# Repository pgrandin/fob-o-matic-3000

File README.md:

# fob-o-matic-3000
The Fob-O-Matic 3000

At my favorite Hackerspace, Ace Monster Toys (https://www.acemonstertoys.org/), members get 24x7 access using their fob.

When a new member wants to join the community, we need an easy way to assign them a fob. Our fobs are pre-bundled in
individual enveloppes with the sign-in instructions. This tool is a simple project that allows us to quickly get the fob
number when we are preparing a batch of keys.

The box was 3D printed and designed for this project. 

Parts list :
 - 1 Arduino Uno R3 (https://www.amazon.com/Arduino-Uno-R3-Microcontroller-A000066/dp/B008GRTSV6) 
 - 1 cheap Oled display (https://www.amazon.com/gp/product/B00O2LLT30)
 - 1 Parallax RFID reader (https://www.amazon.com/gp/product/B00B88HFPG). 

The result:

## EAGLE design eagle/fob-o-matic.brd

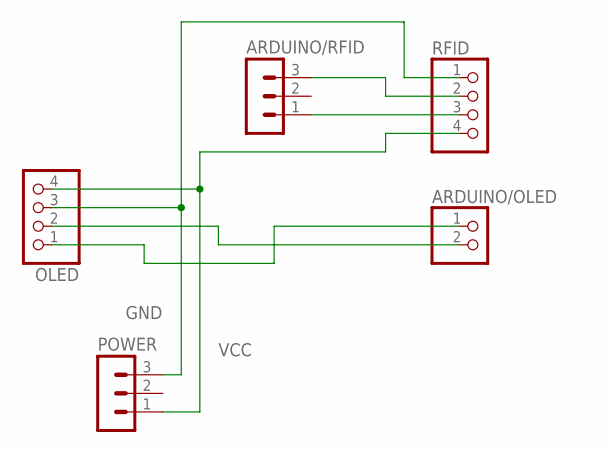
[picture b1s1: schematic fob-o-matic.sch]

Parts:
ARDUINO/OLED: PINHD-1X2; 1X02
ARDUINO/RFID: MA03-1
OLED: PINHD-1X4/90; 1X04/90
POWER: MA03-1
RFID: PINHD-1X4/90; 1X04/90

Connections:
/ENABLE: ARDUINO/RFID.1, RFID.3
GND: OLED.3, POWER.3, RFID.1
RX: ARDUINO/RFID.3, RFID.2
SCL: ARDUINO/OLED.2, OLED.2
SDA: ARDUINO/OLED.1, OLED.1
VCC: OLED.4, POWER.1, RFID.4

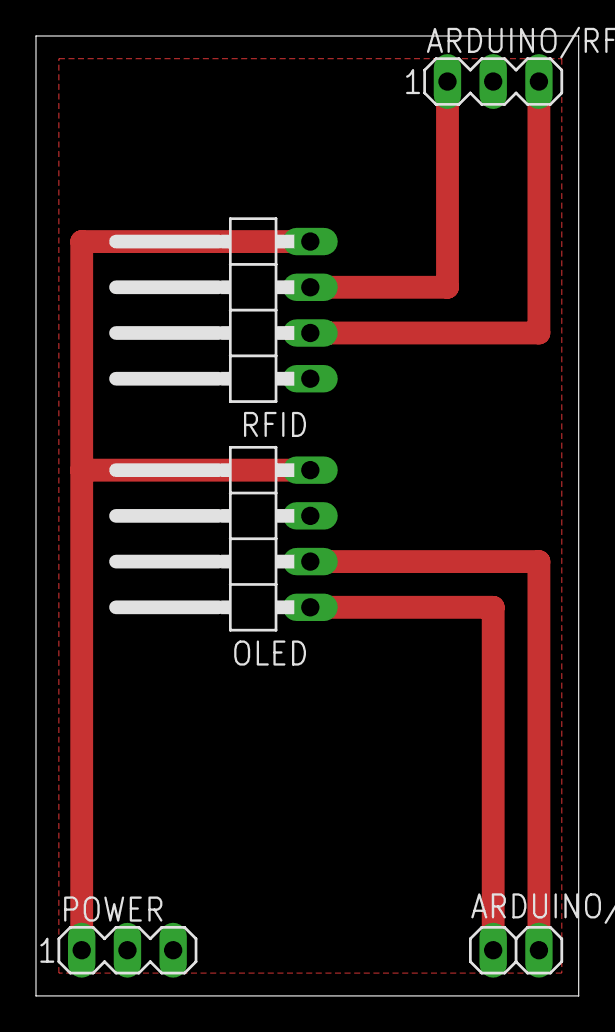
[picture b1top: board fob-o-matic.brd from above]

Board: 2 copper layers, 30.1 x 53.3 mm, 5 parts (0 on the bottom side), 6 nets.

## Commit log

2017-01-09 Initial code import
2017-01-09 Fixed typo in filename
2017-01-09 Expanded README
